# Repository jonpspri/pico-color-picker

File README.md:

# Pico Color Picker

## Acknowledgments

I have included (or borrowed shamelessly) from the following sources:

* FreeRTOS
* FreeType2
* pico-ssd1306
* rxi/log.c

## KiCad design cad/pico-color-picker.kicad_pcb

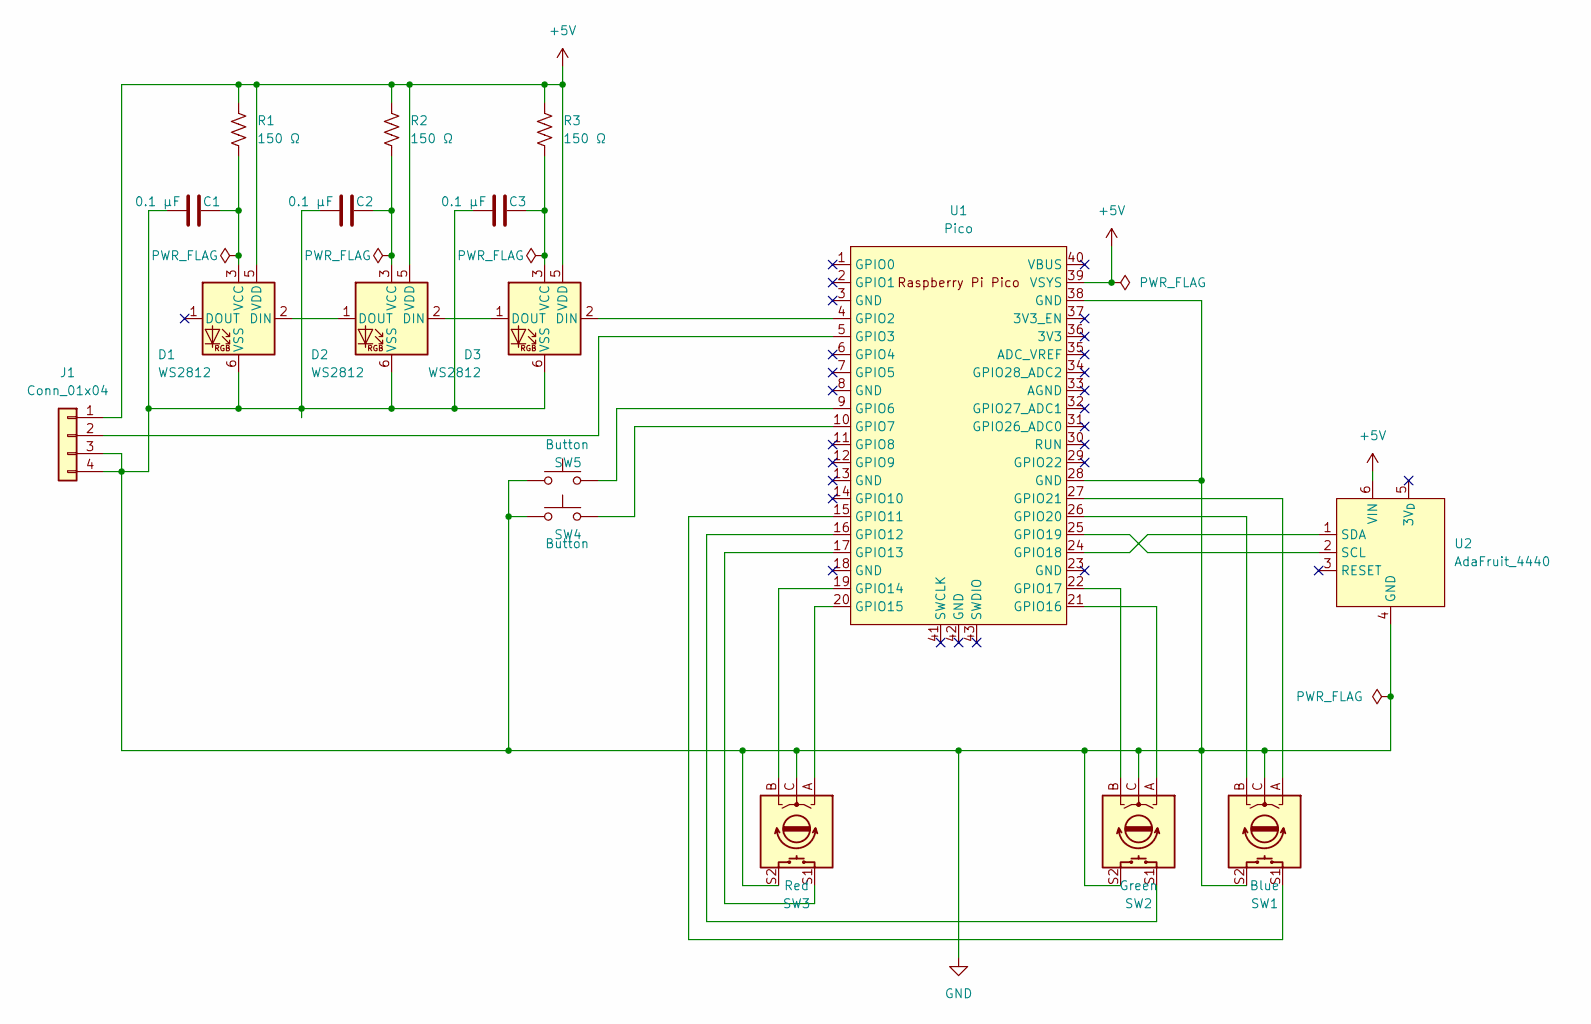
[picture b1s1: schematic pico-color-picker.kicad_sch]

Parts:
C1, C2, C3: 0.1 µF; C_0201_0603Metric; Mfr Part Number AC0201KRX6S5BB104
D1, D2, D3: WS2812; LED_WS2812_PLCC6_5.0x5.0mm_P1.6mm; Mfr Part Number COM-20175
J1: Conn_01x04; PinSocket_1x04_P2.50mm_Vertical
R1, R2, R3: 150 Ω; R_0402_1005Metric; Mfr Part Number RMCF0402FT150R
SW1: Blue; RotaryEncoder_Alps_EC11E-Switch_Vertical_H20mm; Mfr Part Number PEC12R-4220F-S0024
SW2: Green; RotaryEncoder_Alps_EC11E-Switch_Vertical_H20mm; Mfr Part Number PEC12R-4220F-S0024
SW3: Red; RotaryEncoder_Alps_EC11E-Switch_Vertical_H20mm; Mfr Part Number PEC12R-4220F-S0024
SW4, SW5: Button; SW_PUSH-12mm
U1: Pico; RPi_Pico_SMD_TH; Mfr Part Number SC0915
U2: AdaFruit_4440; Mfr Part Number 4440

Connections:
GND: C1.1, C2.1, C3.1, D1.6 (VSS), D2.6 (VSS), D3.6 (VSS), J1.3, J1.4, SW1.C, SW1.S2, SW2.C, SW2.S2, SW3.C, SW3.S2, SW4.2, SW5.2, U1.28 (GND), U1.38 (GND), U2.4 (GND)
unnamed: C1.2, D1.3 (VCC), R1.2
unnamed: C2.2, D2.3 (VCC), R2.2
unnamed: C3.2, D3.3 (VCC), R3.2
unnamed: D1.2 (DIN), D2.1 (DOUT)
unnamed: D2.2 (DIN), D3.1 (DOUT)
unnamed: D3.2 (DIN), U1.4 (GPIO2)
unnamed: J1.2, U1.5 (GPIO3)
unnamed: SW1.A, U1.27 (GPIO21)
unnamed: SW1.B, U1.26 (GPIO20)
unnamed: SW1.S1, U1.15 (GPIO11)
unnamed: SW2.A, U1.21 (GPIO16)
unnamed: SW2.B, U1.22 (GPIO17)
unnamed: SW2.S1, U1.16 (GPIO12)
unnamed: SW3.A, U1.20 (GPIO15)
unnamed: SW3.B, U1.19 (GPIO14)
unnamed: SW3.S1, U1.17 (GPIO13)
unnamed: SW4.1, U1.10 (GPIO7)
unnamed: SW5.1, U1.9 (GPIO6)
unnamed: U1.24 (GPIO18), U2.1 (SDA)
unnamed: U1.25 (GPIO19), U2.2 (SCL)

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
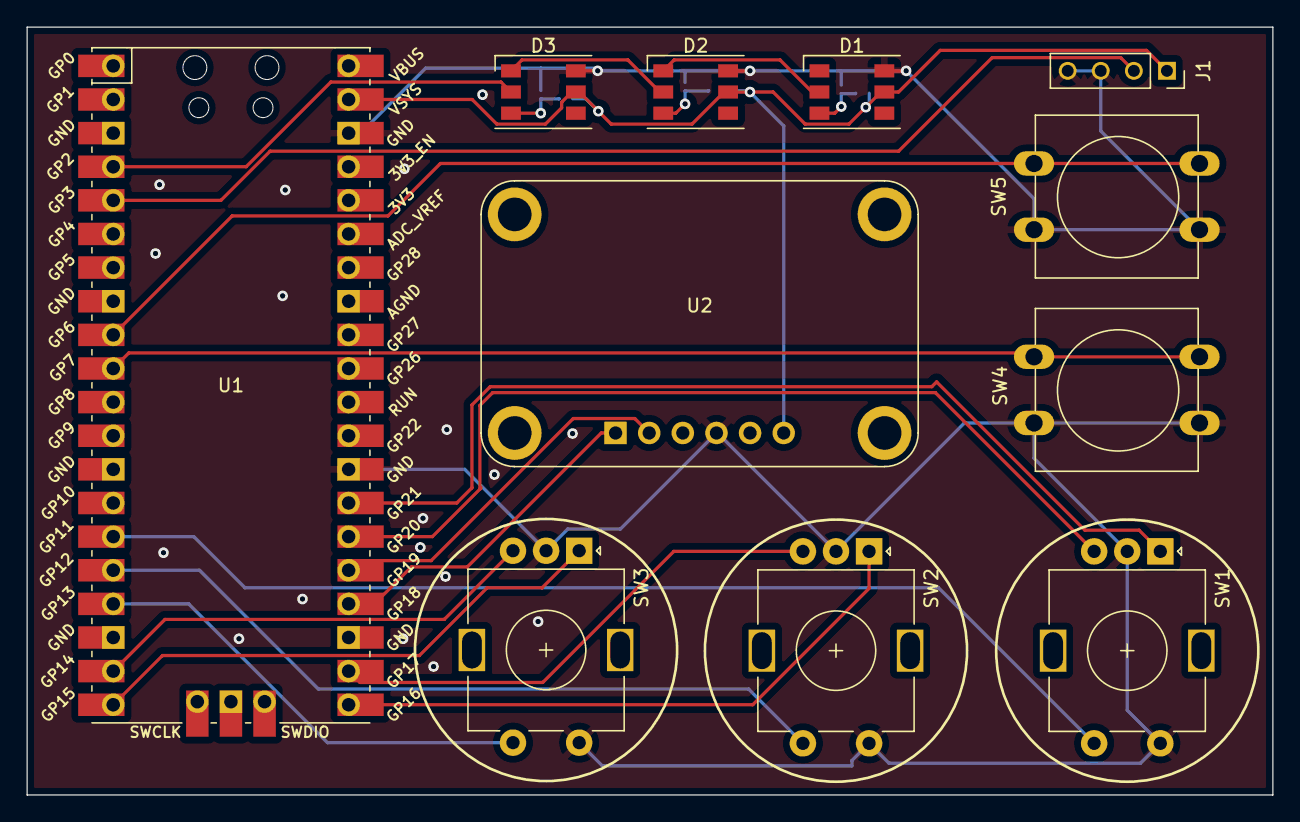
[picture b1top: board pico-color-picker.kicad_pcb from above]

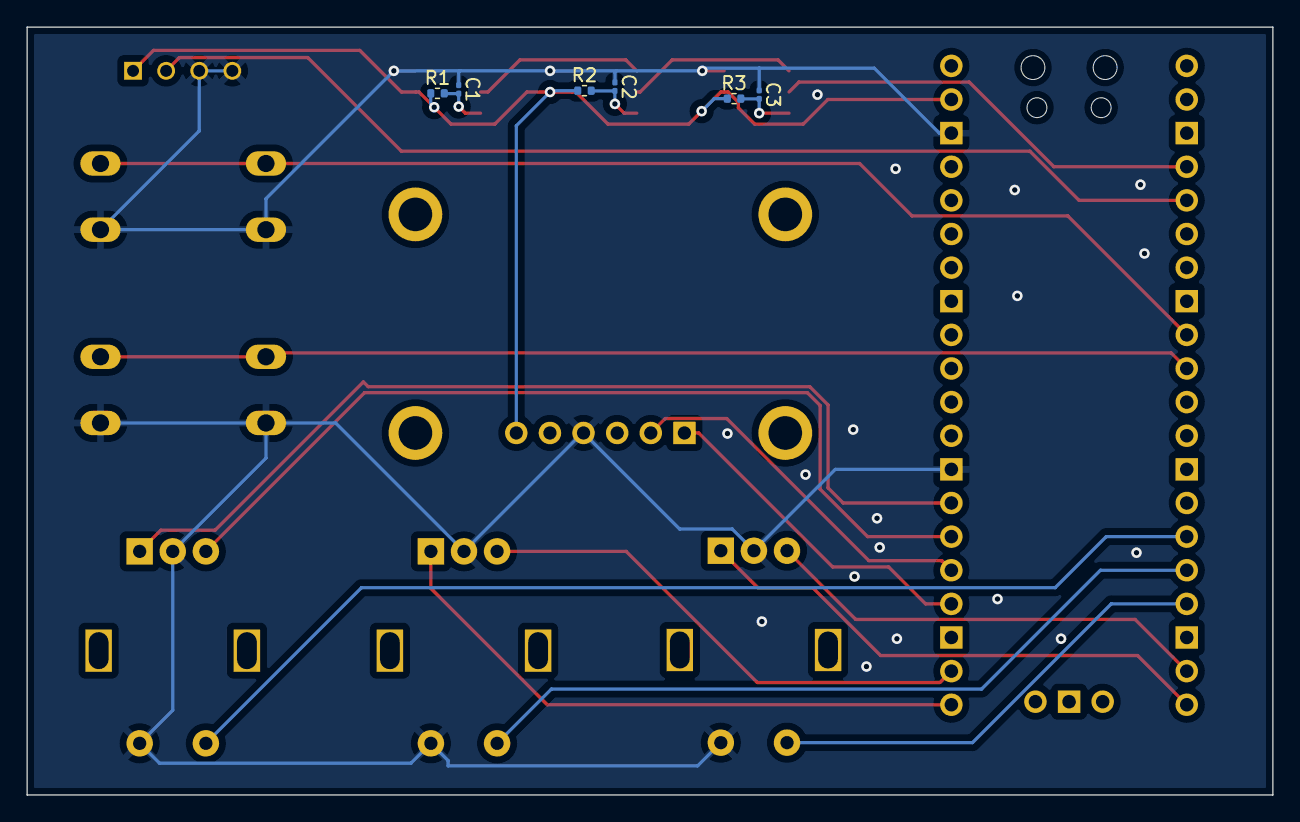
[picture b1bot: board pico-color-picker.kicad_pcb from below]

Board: 2 copper layers, 94.1 x 58.0 mm, 17 parts (6 on the bottom side), 22 nets.

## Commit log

2022-09-08 Initial Experiment with Plex Mono
2022-09-11 Rotary Encoders work
2022-09-13 Tuned rotary encoder code and added LEDs.
2022-09-13 Adding Buttons
2022-09-14 Schematic tuning
2022-09-14 Parameterize to build.
2022-09-14 Use only 1 PIO for REs
2022-09-19 Tinker with PCB layout.
2022-09-20 PCB Cleanup
2022-09-23 Optimize FreeType build somewhat.
2022-09-24 FreeRTOS is working!
2022-09-25 Update logging library.
2022-09-28 Switch to bitmap fonts.
2022-09-28 Readable submodule
2022-10-02 Begin move to C++
2022-10-04 Working C version.
2022-10-04 Abstract bitmap and Doxygen
2022-10-04 Bitmap interface for ssd1306.
2022-10-04 Tweak memory mgmt to FreeRTOS
2022-10-04 Start of the colors menu.
2022-10-06 Refactoring for generalization.
2022-10-07 First iteration of menu processing - no buttons yet.
2022-10-07 Simplify default button code.
2022-10-07 Futher refactoring to support multi-menus
2022-10-08 Some standardization and menu additions.
2022-10-08 Clean up cad directory.
2022-10-11 Forward button working.
2022-10-11 Menu to color navigation.
2022-10-11 Label on RGB Encoder screen.
2022-10-11 Rationalize callbacks for context
2022-10-12 Refactor note colors into a separate module.
2022-10-12 Transition to stack for contexts
2022-10-13 Pass LED info to task.
2022-10-13 Get the Line 1 rendering to work.
2022-10-15 Switch to builder pattern for context.
2022-10-15 Factor in multi-menu code
2022-10-16 Formatting changes and another step toward chord.
2022-10-16 Reduce malloc dependency
2022-10-16 The chord menu works!
2022-10-16 And chords are awesome!
2022-10-17 Add a main menu.
2022-10-21 Formatting updates.
2023-01-02 Add work items to TODO
